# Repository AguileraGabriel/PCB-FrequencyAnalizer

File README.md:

# TD3-FrequencyAnalizer

Proyecto de KiCad para el Analizador de Frecuencias (TD3).

## Descripción del Proyecto

Este es un proyecto de diseño de PCB desarrollado en KiCad 10.0.4.

## Estructura del Proyecto

*   **`TD3-FrequencyAnalizer.kicad_pro`**: Archivo de proyecto de KiCad.
*   **`TD3-FrequencyAnalizer.kicad_sch`**: Esquema del circuito.
*   **`TD3-FrequencyAnalizer.kicad_pcb`**: Diseño del circuito impreso (PCB).
*   **`.gitignore`**: Exclusiones de Git para evitar subir archivos temporales y copias de seguridad de KiCad.

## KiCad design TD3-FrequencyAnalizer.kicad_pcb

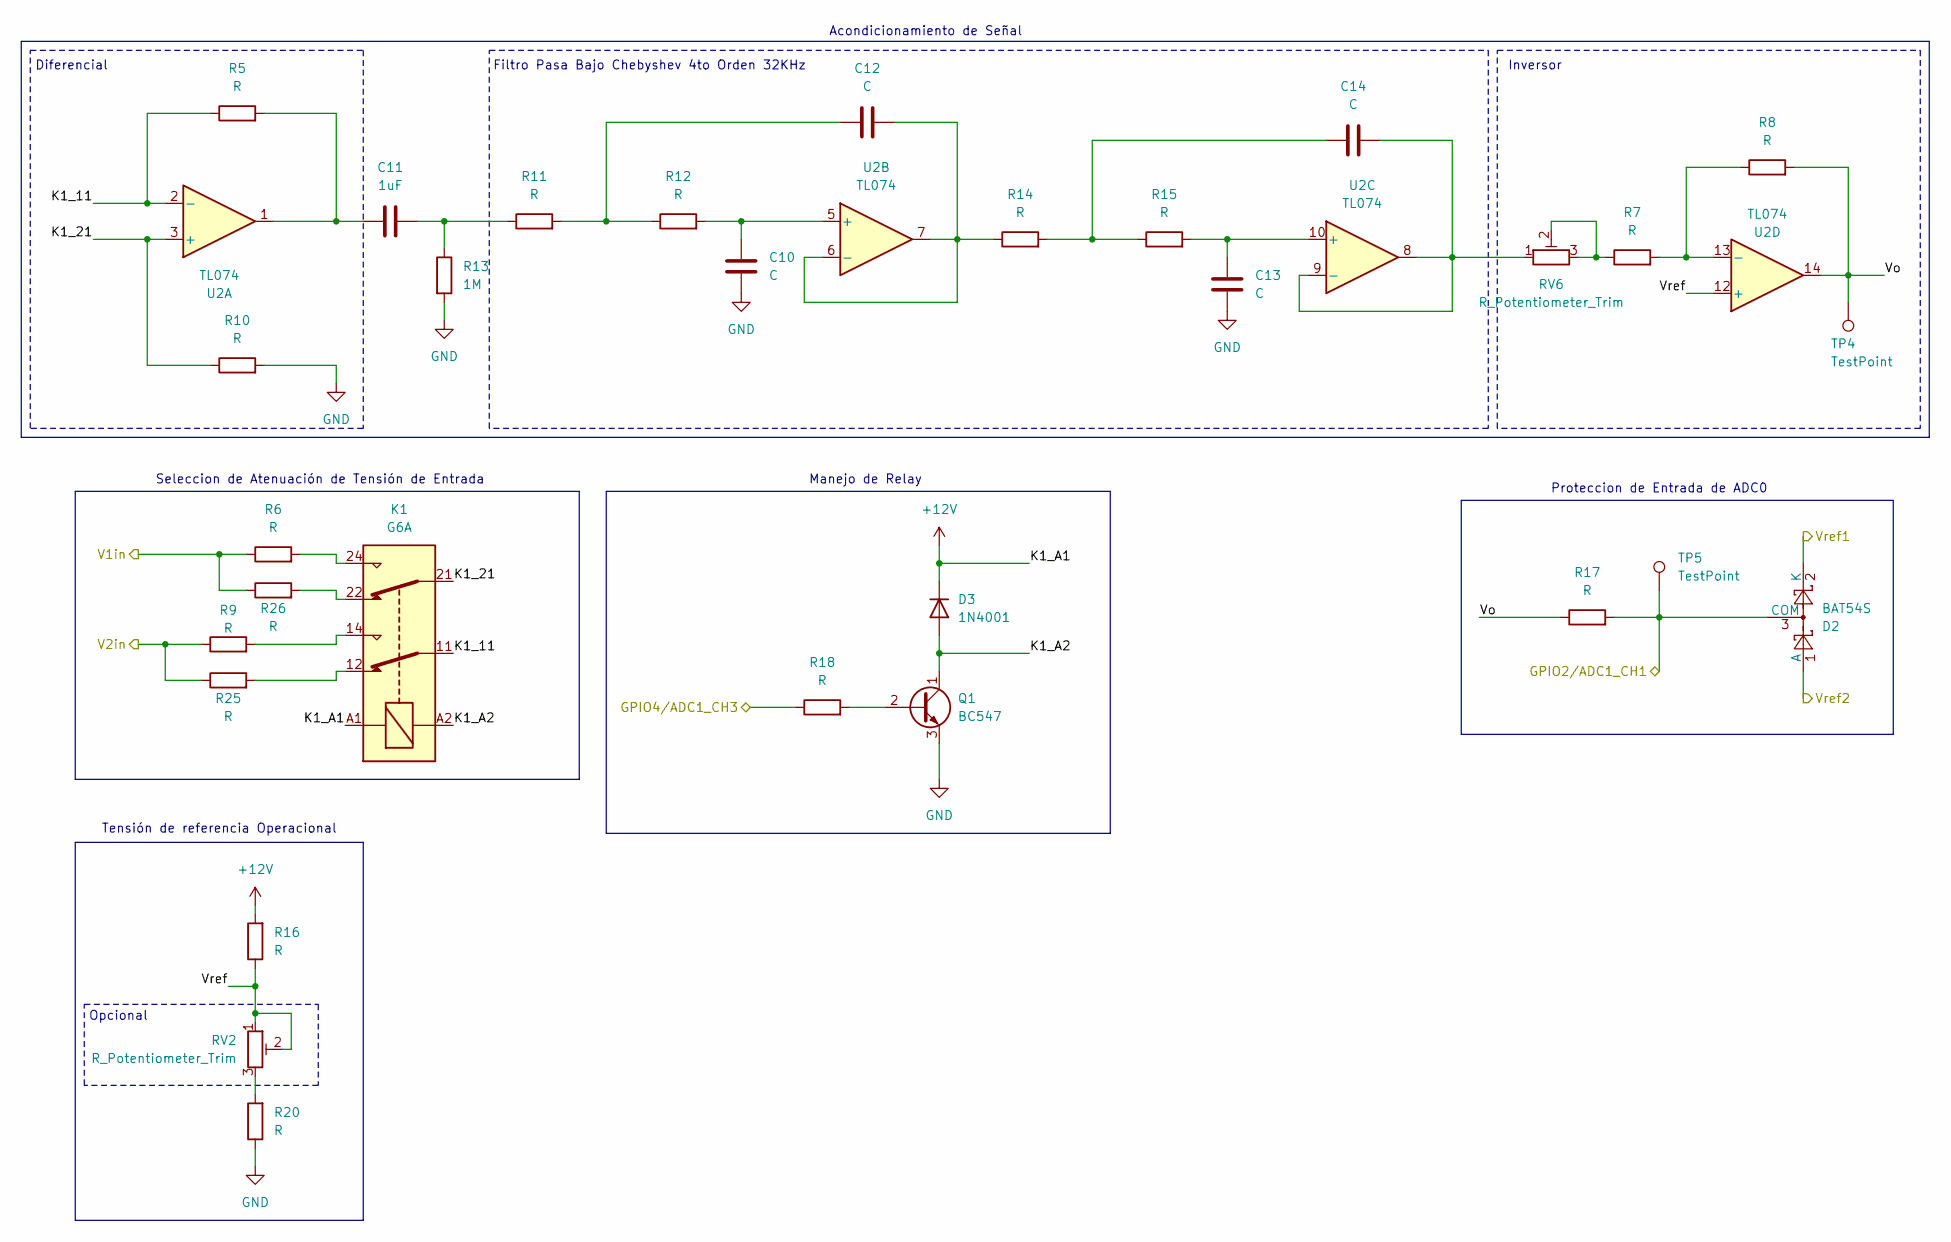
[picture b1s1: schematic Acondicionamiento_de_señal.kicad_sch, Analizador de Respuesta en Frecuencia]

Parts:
C10, C12, C13, C14: C; C_Disc_D7.5mm_W2.5mm_P5.00mm
C11: 1uF; C_Disc_D7.5mm_W2.5mm_P5.00mm
D2: BAT54S; SOT-23
D3: 1N4001; D_DO-41_SOD81_P10.16mm_Horizontal
K1: G6A; Relay_DPDT_Omron_G6A
Q1: BC547; TO-92_HandSolder
R5, R6, R7, R8, R9, R10, R11, R12, R14, R15, R16, R17, R18, R20, R25, R26: R; R_Axial_DIN0207_L6.3mm_D2.5mm_P10.16mm_Horizontal
R13: 1M; R_Axial_DIN0207_L6.3mm_D2.5mm_P10.16mm_Horizontal
RV2, RV6: R_Potentiometer_Trim; Potentiometer_Bourns_3266Y_Vertical
TP4, TP5: TestPoint; TestPoint_Loop_D2.50mm_Drill1.0mm
U2: TL074; CERDIP-14_W7.62mm_SideBrazed_LongPads_Socket

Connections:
+12V: D3.1 (K), K1.A1, R16.2; also elsewhere on the board
/Acondicionamiento de Señal de Entrada/GPIO2/ADC1_CH1: D2.3 (COM), R17.2, TP5.1 (1_1); also elsewhere on the board
/Acondicionamiento de Señal de Entrada/GPIO4/ADC1_CH3: R18.1; also elsewhere on the board
/Acondicionamiento de Señal de Entrada/K1_11: K1.11, R5.1, U2.2 (-)
/Acondicionamiento de Señal de Entrada/K1_21: K1.21, R10.1, U2.3 (+)
/Acondicionamiento de Señal de Entrada/K1_A2: D3.2 (A), K1.A2, Q1.1 (C)
/Acondicionamiento de Señal de Entrada/V1in: R6.1, R26.1; also elsewhere on the board
/Acondicionamiento de Señal de Entrada/V2in: R9.1, R25.1; also elsewhere on the board
/Acondicionamiento de Señal de Entrada/Vo: R8.2, R17.1, TP4.1 (1_1), U2.14
/Acondicionamiento de Señal de Entrada/Vref: R16.1, RV2.1, RV2.2, U2.12 (+)
/Acondicionamiento de Señal de Entrada/Vref1: D2.2 (K); also elsewhere on the board
/Acondicionamiento de Señal de Entrada/Vref2: D2.1 (A); also elsewhere on the board
GND: C10.2, C13.2, Q1.3 (E), R10.2, R13.2, R20.1; also elsewhere on the board
unnamed: C11.1, R5.2, U2.1
unnamed: C11.2, R11.1, R13.1
unnamed: C12.1, R11.2, R12.1
unnamed: C14.1, R14.2, R15.1
unnamed: K1.12, R25.2
unnamed: K1.14, R9.2
unnamed: K1.22, R26.2
unnamed: K1.24, R6.2
unnamed: Q1.2 (B), R18.2
unnamed: R7.1, RV6.2, RV6.3
unnamed: R20.2, RV2.3
unnamed: C10.1, R12.2, U2.5 (+)
unnamed: C12.2, R14.1, U2.6 (-), U2.7
unnamed: C13.1, R15.2, U2.10 (+)
unnamed: C14.2, RV6.1, U2.8, U2.9 (-)
unnamed: R7.2, R8.1, U2.13 (-)

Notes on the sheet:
Manejo de Relay
Opcional
Filtro Pasa Bajo Chebyshev 4to Orden 32KHz
Acondicionamiento de Señal
Seleccion de Atenuación de Tensión de Entrada
Diferencial
Tensión de referencia Operacional
Proteccion de Entrada de ADC0
Inversor

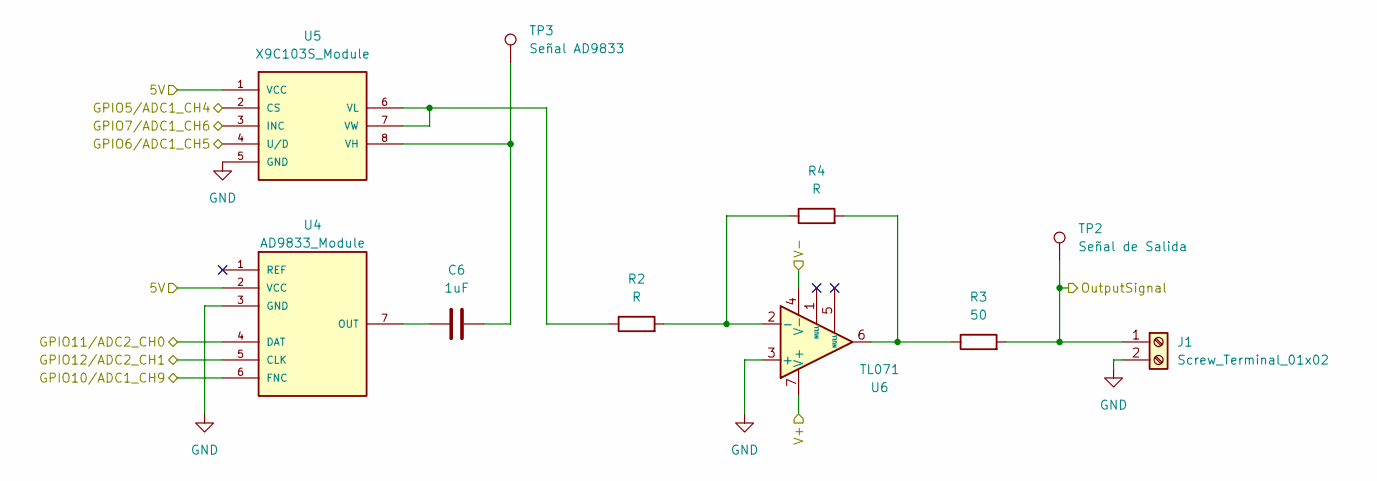
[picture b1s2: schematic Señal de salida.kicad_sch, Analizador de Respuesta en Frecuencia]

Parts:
C6: 1uF; C_Disc_D7.5mm_W2.5mm_P5.00mm
J1: Screw_Terminal_01x02; TerminalBlock_MaiXu_MX126-5.0-02P_1x02_P5.00mm
R2, R4: R; R_Axial_DIN0207_L6.3mm_D2.5mm_P10.16mm_Horizontal
R3: 50; R_Axial_DIN0207_L6.3mm_D2.5mm_P10.16mm_Horizontal
TP2: Señal de Salida; TestPoint_Loop_D2.50mm_Drill1.0mm
TP3: Señal AD9833; TestPoint_Loop_D2.50mm_Drill1.0mm
U4: AD9833_Module
U5: X9C103S_Module
U6: TL071; CERDIP-8_W7.62mm_SideBrazed_LongPads_Socket

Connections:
+12V: U6.7 (V+); also elsewhere on the board
-12V: U6.4 (V-); also elsewhere on the board
/ESP32-S3/5V: U4.2 (VCC), U5.1 (VCC); also elsewhere on the board
/ESP32-S3/GPIO5/ADC1_CH4: U5.2 (CS); also elsewhere on the board
/ESP32-S3/GPIO6/ADC1_CH5: U5.4 (U/D); also elsewhere on the board
/ESP32-S3/GPIO7/ADC1_CH6: U5.3 (INC); also elsewhere on the board
/ESP32-S3/GPIO10/ADC1_CH9: U4.6 (FNC); also elsewhere on the board
/ESP32-S3/GPIO11/ADC2_CH0: U4.4 (DAT); also elsewhere on the board
/ESP32-S3/GPIO12/ADC2_CH1: U4.5 (CLK); also elsewhere on the board
/Medición de Señal Inyectada/OutputSignal: J1.1, R3.2, TP2.1 (1_1); also elsewhere on the board
GND: J1.2, U4.3 (GND), U5.5 (GND), U6.3 (+); also elsewhere on the board
unnamed: R3.1, R4.2, U6.6
unnamed: C6.1, U4.7 (OUT)
unnamed: C6.2, TP3.1 (1_1), U5.8 (VH)
unnamed: R2.1, U5.6 (VL), U5.7 (VW)
unnamed: R2.2, R4.1, U6.2 (-)

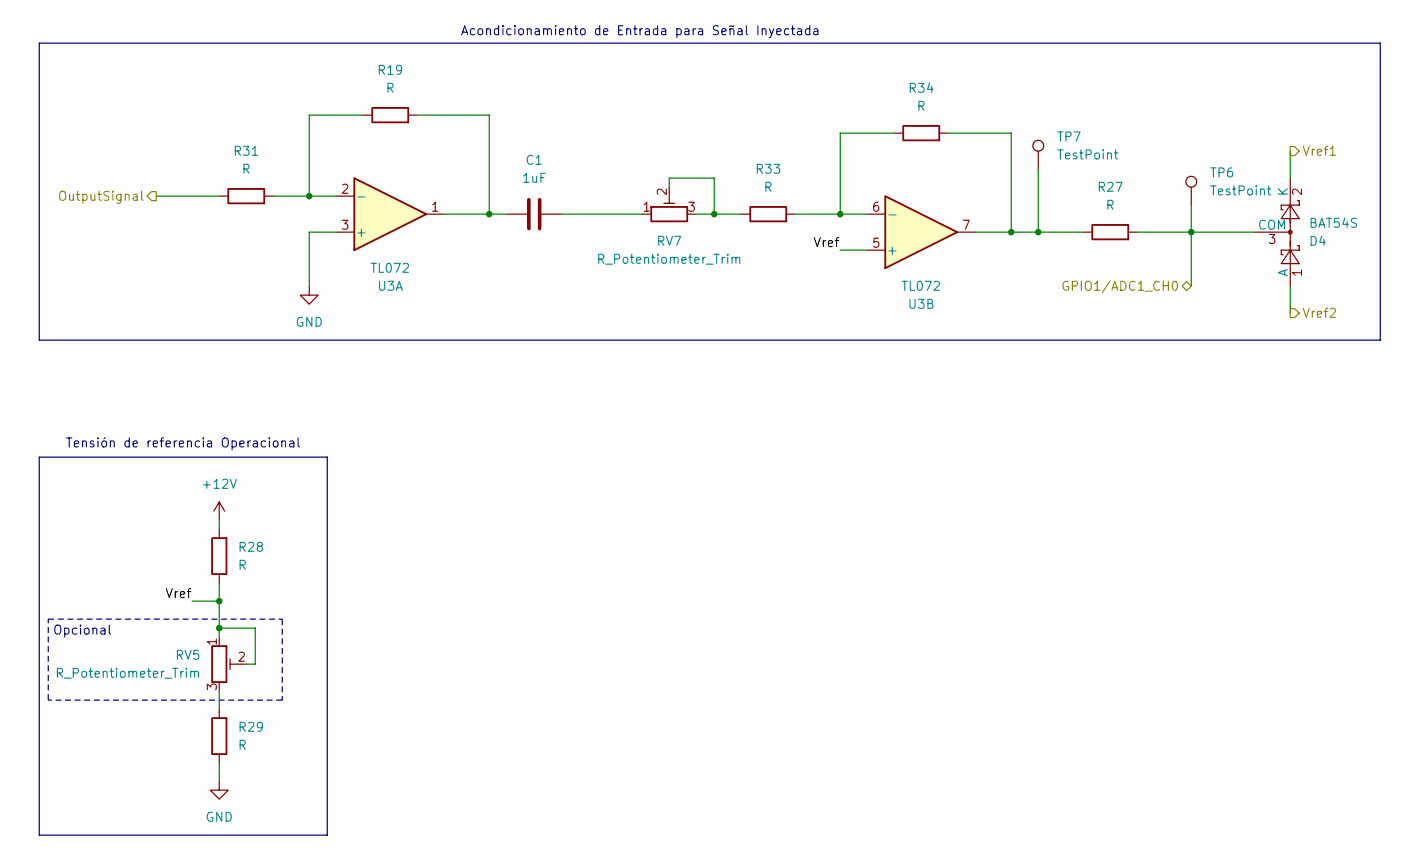
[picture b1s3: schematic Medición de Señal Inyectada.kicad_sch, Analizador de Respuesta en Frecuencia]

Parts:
C1: 1uF; C_Disc_D7.5mm_W2.5mm_P5.00mm
D4: BAT54S; SOT-23
R19, R27, R28, R29, R31, R33, R34: R; R_Axial_DIN0207_L6.3mm_D2.5mm_P10.16mm_Horizontal
RV5, RV7: R_Potentiometer_Trim; Potentiometer_Bourns_3266Y_Vertical
TP6, TP7: TestPoint; TestPoint_Loop_D2.50mm_Drill1.0mm
U3: TL072; CERDIP-8_W7.62mm_SideBrazed_LongPads_Socket

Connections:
+12V: R28.2; also elsewhere on the board
/Acondicionamiento de Señal de Entrada/Vref1: D4.2 (K); also elsewhere on the board
/Acondicionamiento de Señal de Entrada/Vref2: D4.1 (A); also elsewhere on the board
/ESP32-S3/GPIO1/ADC1_CH0: D4.3 (COM), R27.2, TP6.1 (1_1); also elsewhere on the board
/Medición de Señal Inyectada/OutputSignal: R31.1; also elsewhere on the board
/Medición de Señal Inyectada/Vref: R28.1, RV5.1, RV5.2, U3.5 (+)
GND: R29.1, U3.3 (+); also elsewhere on the board
unnamed: C1.1, R19.2, U3.1
unnamed: C1.2, RV7.1
unnamed: R27.1, R34.2, TP7.1 (1_1), U3.7
unnamed: R29.2, RV5.3
unnamed: R33.1, RV7.2, RV7.3
unnamed: R19.1, R31.2, U3.2 (-)
unnamed: R33.2, R34.1, U3.6 (-)

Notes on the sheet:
Opcional
Acondicionamiento de Entrada para Señal Inyectada
Tensión de referencia Operacional

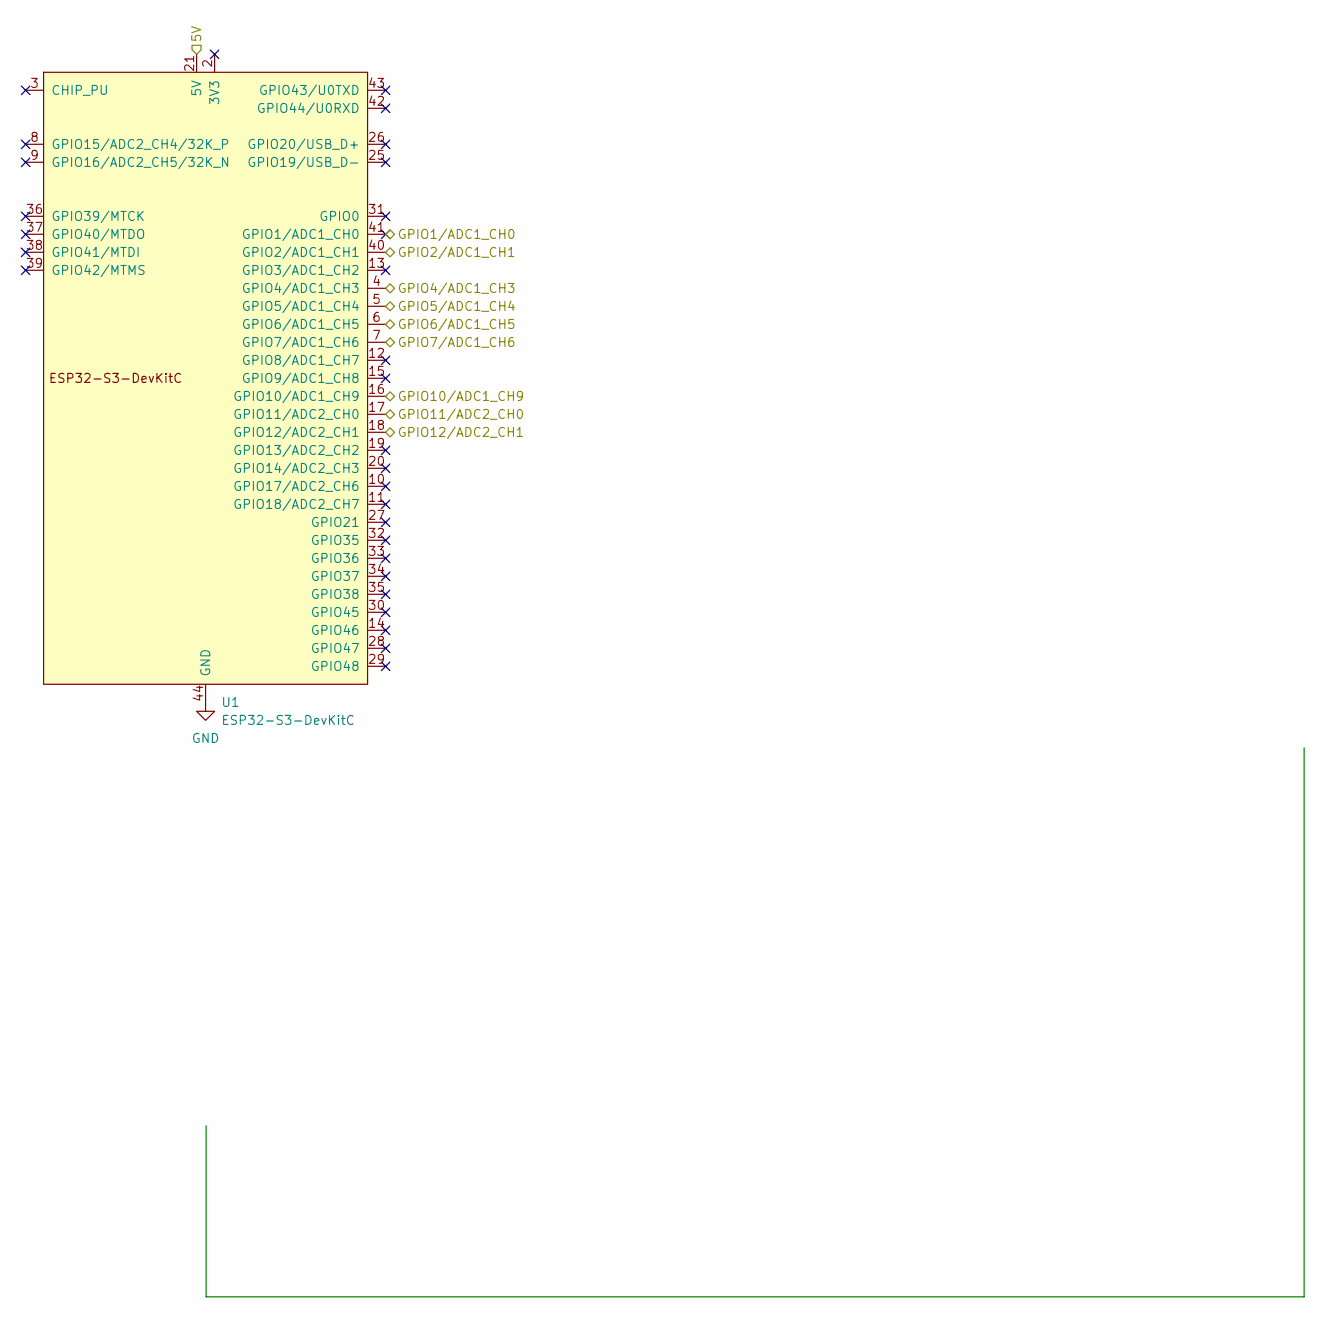
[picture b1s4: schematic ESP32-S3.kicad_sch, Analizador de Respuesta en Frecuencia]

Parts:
U1: ESP32-S3-DevKitC

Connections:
/Acondicionamiento de Señal de Entrada/GPIO2/ADC1_CH1: U1.40 (GPIO2/ADC1_CH1); also elsewhere on the board
/Acondicionamiento de Señal de Entrada/GPIO4/ADC1_CH3: U1.4 (GPIO4/ADC1_CH3); also elsewhere on the board
/ESP32-S3/5V: U1.21 (5V); also elsewhere on the board
/ESP32-S3/GPIO1/ADC1_CH0: U1.41 (GPIO1/ADC1_CH0); also elsewhere on the board
/ESP32-S3/GPIO5/ADC1_CH4: U1.5 (GPIO5/ADC1_CH4); also elsewhere on the board
/ESP32-S3/GPIO6/ADC1_CH5: U1.6 (GPIO6/ADC1_CH5); also elsewhere on the board
/ESP32-S3/GPIO7/ADC1_CH6: U1.7 (GPIO7/ADC1_CH6); also elsewhere on the board
/ESP32-S3/GPIO10/ADC1_CH9: U1.16 (GPIO10/ADC1_CH9); also elsewhere on the board
/ESP32-S3/GPIO11/ADC2_CH0: U1.17 (GPIO11/ADC2_CH0); also elsewhere on the board
/ESP32-S3/GPIO12/ADC2_CH1: U1.18 (GPIO12/ADC2_CH1); also elsewhere on the board
GND: U1.22 (GND), U1.23 (GND), U1.24 (GND), U1.44 (GND); also elsewhere on the board

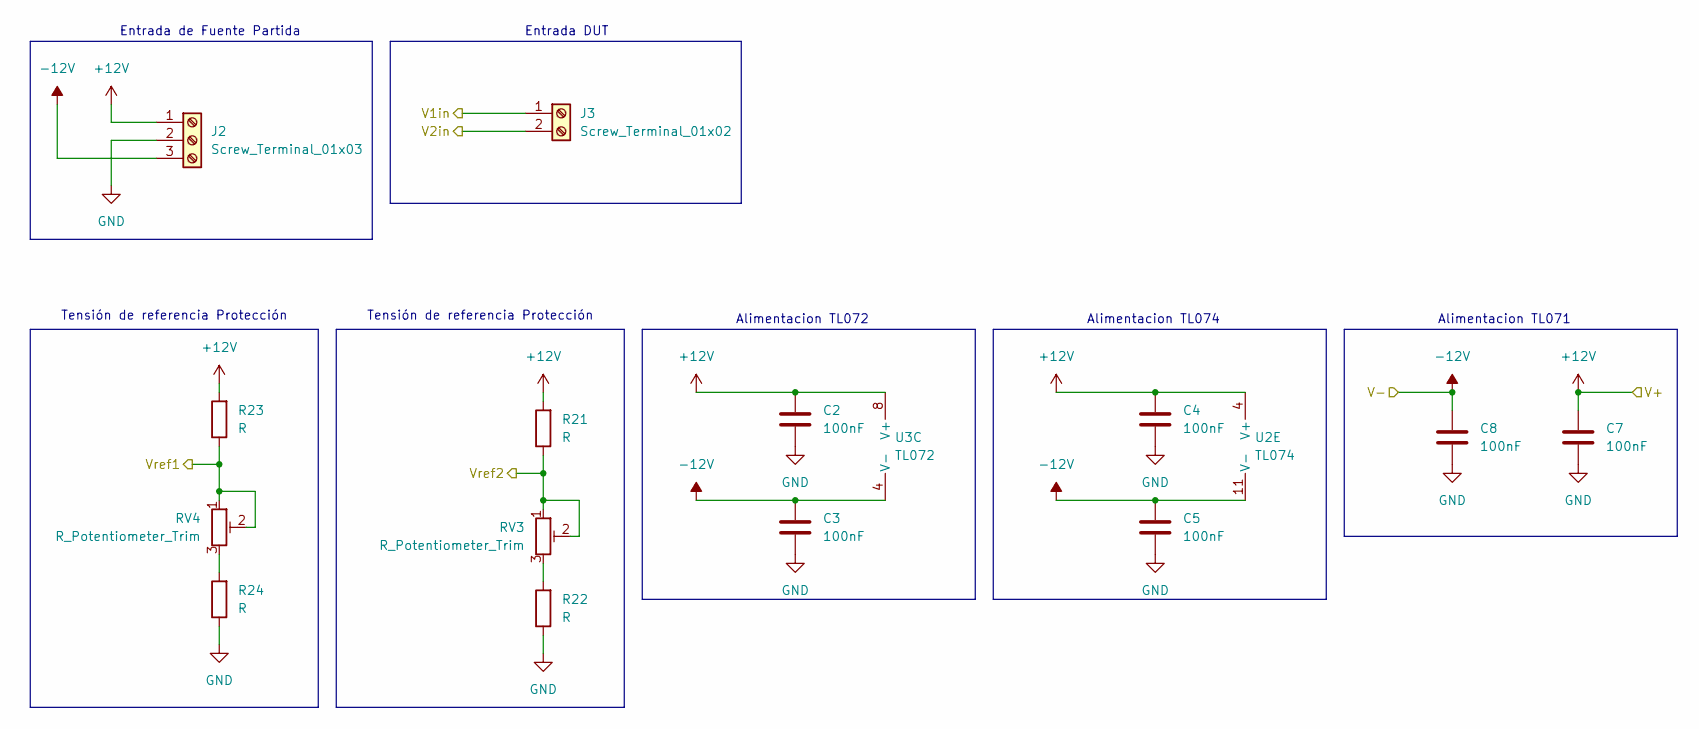
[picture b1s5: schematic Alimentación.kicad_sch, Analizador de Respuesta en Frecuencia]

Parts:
C2, C3, C4, C5, C7, C8: 100nF; C_Disc_D7.5mm_W2.5mm_P5.00mm
J2: Screw_Terminal_01x03; TerminalBlock_MaiXu_MX126-5.0-03P_1x03_P5.00mm
J3: Screw_Terminal_01x02; TerminalBlock_MaiXu_MX126-5.0-02P_1x02_P5.00mm
R21, R22, R23, R24: R; R_Axial_DIN0207_L6.3mm_D2.5mm_P10.16mm_Horizontal
RV3, RV4: R_Potentiometer_Trim; Potentiometer_Bourns_3266Y_Vertical
U2: TL074; CERDIP-14_W7.62mm_SideBrazed_LongPads_Socket
U3: TL072; CERDIP-8_W7.62mm_SideBrazed_LongPads_Socket

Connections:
+12V: C2.1, C4.1, C7.2, J2.1, R21.2, R23.2, U2.4 (V+), U3.8 (V+); also elsewhere on the board
-12V: C3.1, C5.1, C8.2, J2.3, U2.11 (V-), U3.4 (V-); also elsewhere on the board
/Acondicionamiento de Señal de Entrada/V1in: J3.1; also elsewhere on the board
/Acondicionamiento de Señal de Entrada/V2in: J3.2; also elsewhere on the board
/Acondicionamiento de Señal de Entrada/Vref1: R23.1, RV4.1, RV4.2; also elsewhere on the board
/Acondicionamiento de Señal de Entrada/Vref2: R21.1, RV3.1, RV3.2; also elsewhere on the board
GND: C2.2, C3.2, C4.2, C5.2, C7.1, C8.1, J2.2, R22.1, R24.1; also elsewhere on the board
unnamed: R22.2, RV3.3
unnamed: R24.2, RV4.3

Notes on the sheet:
Alimentacion TL071
Tensión de referencia Protección
Alimentacion TL074
Entrada de Fuente Partida
Alimentacion TL072
Entrada DUT

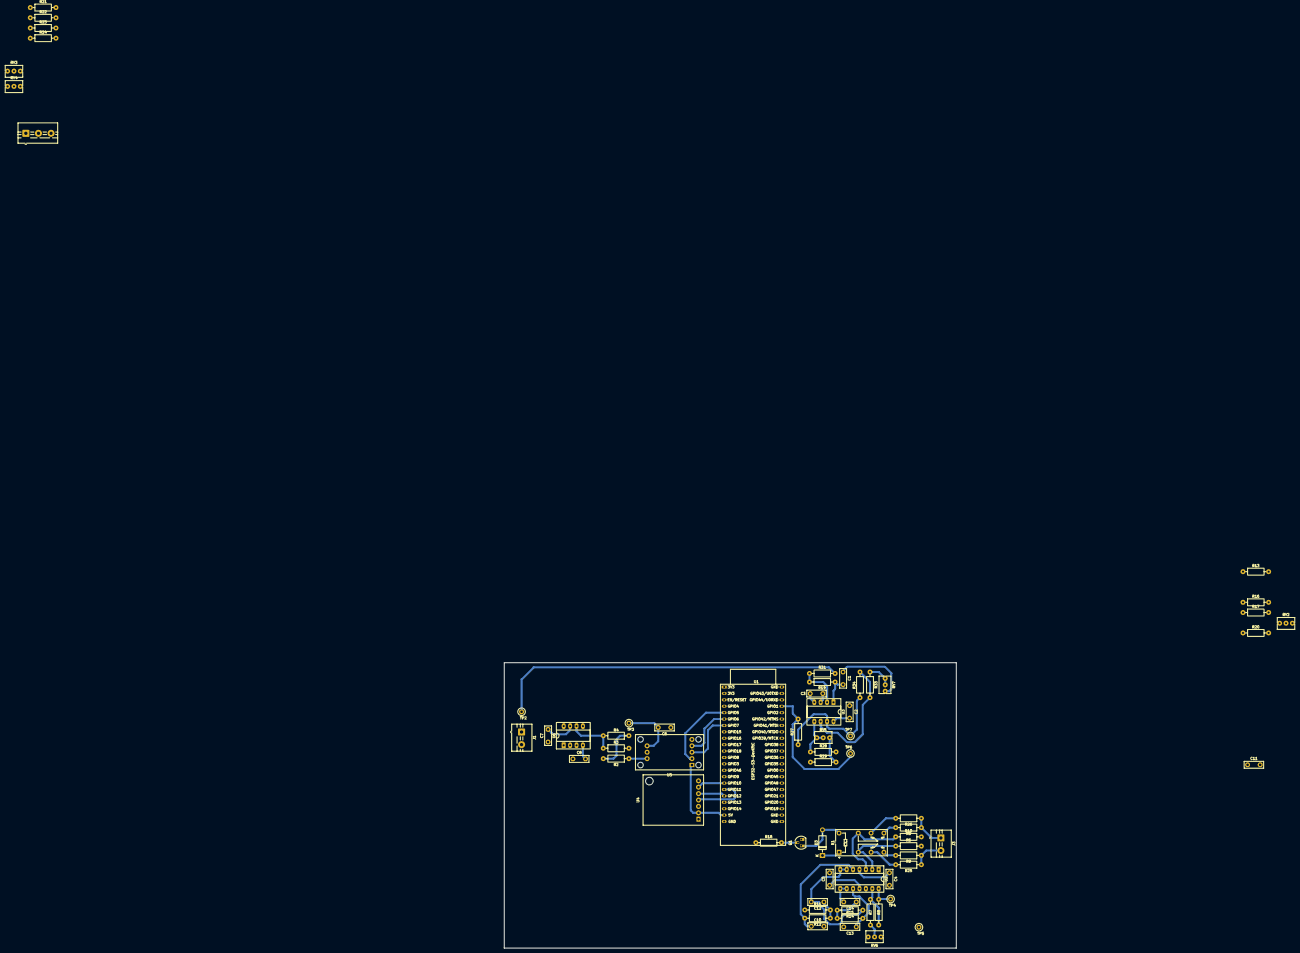
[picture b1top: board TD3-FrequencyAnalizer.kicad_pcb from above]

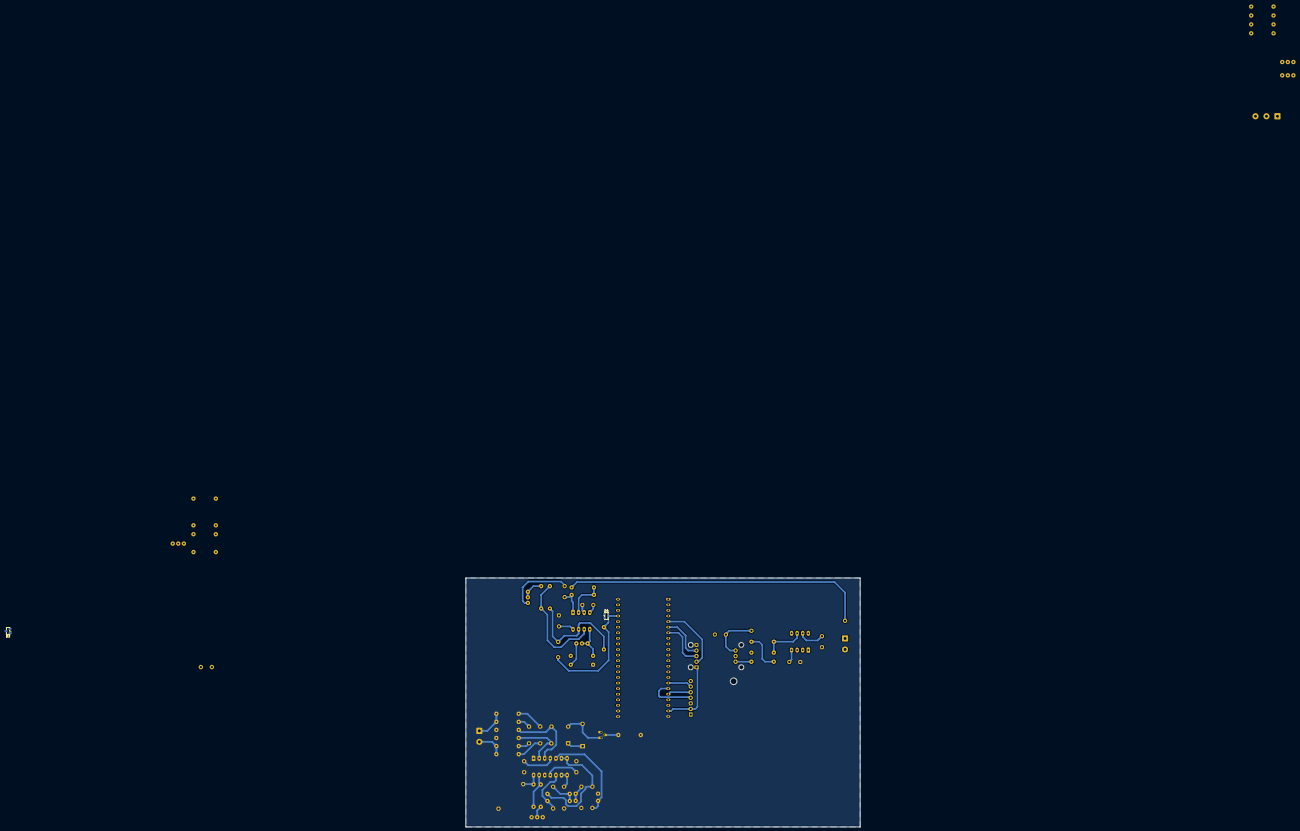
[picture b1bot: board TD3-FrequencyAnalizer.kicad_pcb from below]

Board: 2 copper layers, 179.3 x 113.2 mm, 70 parts (2 on the bottom side), 54 nets.
